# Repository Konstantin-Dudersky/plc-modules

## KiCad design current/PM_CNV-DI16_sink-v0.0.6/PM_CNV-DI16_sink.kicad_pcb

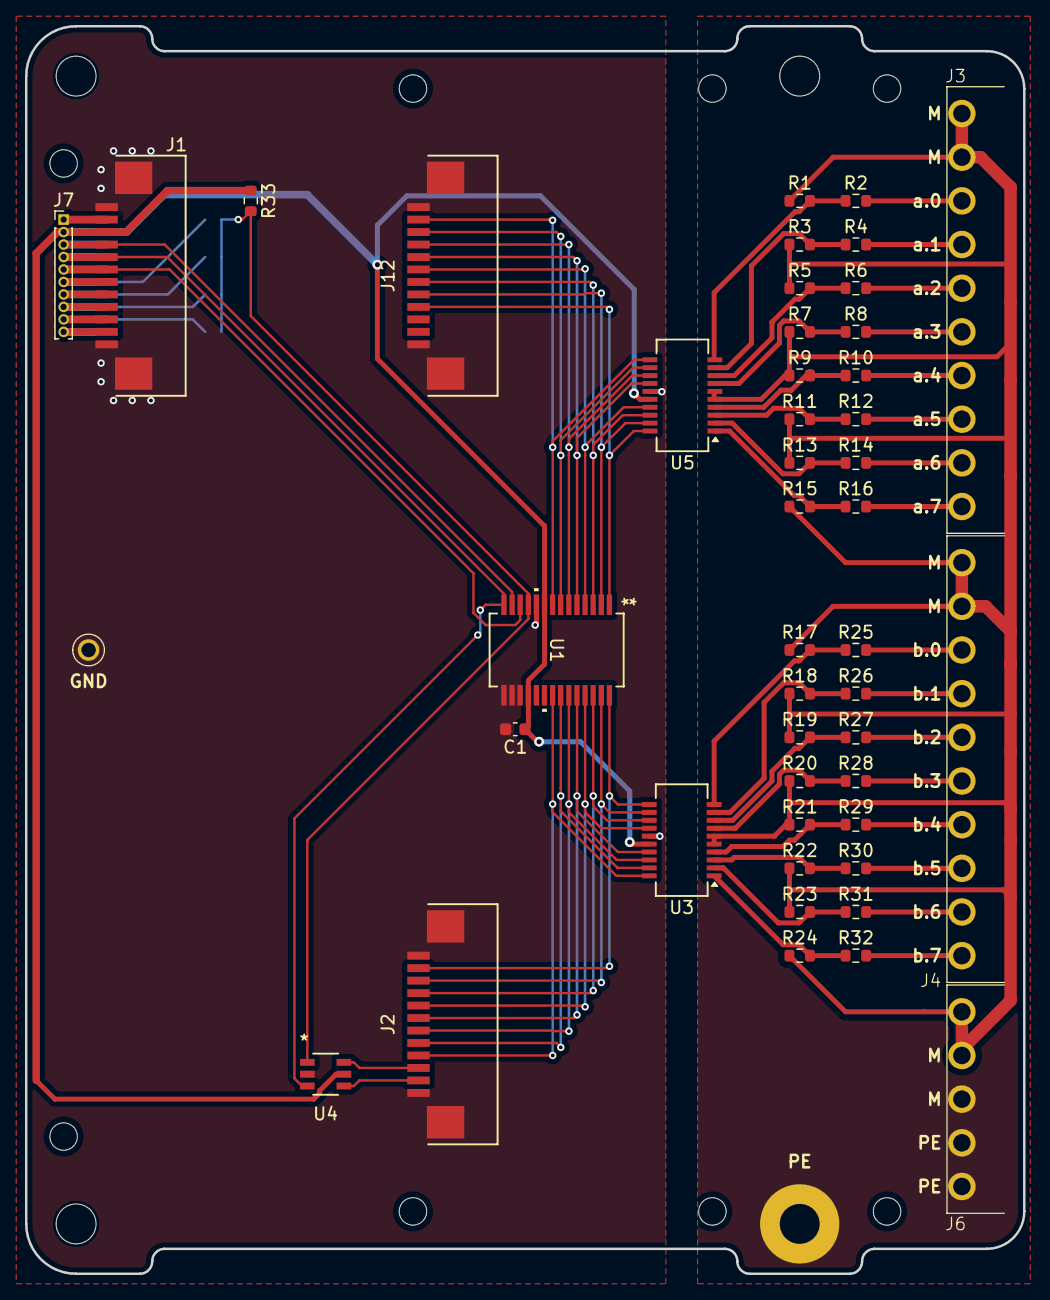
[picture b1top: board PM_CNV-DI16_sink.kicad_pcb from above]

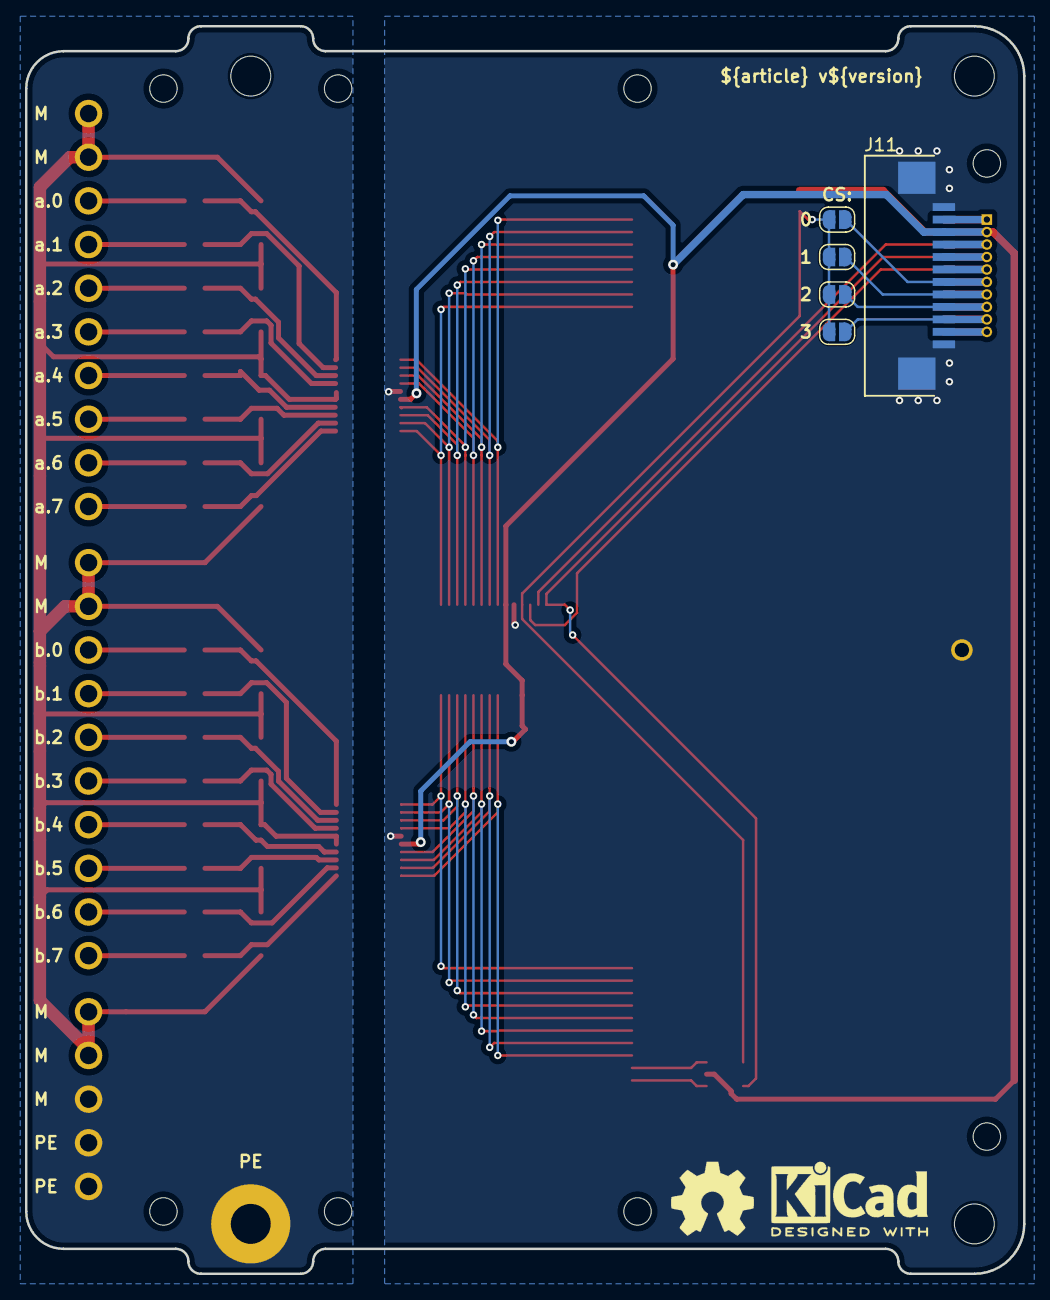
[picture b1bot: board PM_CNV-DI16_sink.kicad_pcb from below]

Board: 2 copper layers, 80.0 x 100.0 mm, 59 parts (7 on the bottom side), 64 nets.

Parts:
C1: 100nF; C_0603_1608Metric
H1, H2, H3: MountingHole; MountingHole_3.2mm_M3
J1, J2, J11, J12: AFA07-S12FCC-00; CONN10_AFA07-S12_JUS
J3, J4: 15EDGRC-3.5-10P
J6: 15EDGRC-3.5-05P
J7: PinHeader_01x10_P1.00_THT_straight; PinHeader_1x10_P1.00mm_Vertical
JP1, JP2, JP3, JP4: SolderJumper_2_Open; SolderJumper-2_P1.3mm_Open_RoundedPad1.0x1.5mm
PE1: PE
R1, R3, R5, R7, R9, R11, R13, R15, R17, R18, R19, R20, R21, R22, R23, R24: 750R; R_0603_1608Metric
R2, R4, R6, R8, R10, R12, R14, R16, R25, R26, R27, R28, R29, R30, R31, R32: 2k7; R_0603_1608Metric
R33: 10k; R_0603_1608Metric
SP1: PM_LED-xx-v0.0.1
U1: MCP23S17_SS; SSOP28_MC_MCH
U2: PM-ESP32C3_v0.0.5
U3, U5: CA-IS3980P; SSOP-20_3.9x8.7mm_P0.635mm
U4: SN74LVC2G14DBVR; DBV6-M
U6: 5117
kicad_logo: KiCad-Logo2_5mm_SilkScreen
oshw_logo: OSHW-Symbol_6.7x6mm_SilkScreen

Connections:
+3.3V_MCU: C1.1, J1.10, J7.2, J11.3, R33.1, U1.9 (VDD), U1.18 (~RESET), U3.16 (VDD), U4.5 (VCC), U5.16 (VDD)
+5V: J1.11, J7.1, J11.2
/CS: JP1.2 (B), JP2.2 (B), JP3.2 (B), JP4.2 (B), R33.2, U1.11 (~CS), U4.1 (1A)
/CS0: J1.6, J7.6, J11.7, JP1.1 (A)
/CS1: J1.5, J7.7, J11.8, JP2.1 (A)
/CS2: J1.4, J7.8, J11.9, JP3.1 (A)
/CS3: J1.3, J7.9, J11.10, JP4.1 (A)
/CS_LED: J2.3, U4.6 (1Y)
/GND_CNV: J3.9, J3.10, J4.9, J4.10, J6.4, J6.5, R1.1, R3.1, R5.1, R7.1, R9.1, R11.1, R13.1, R15.1, R17.1, R18.1, R19.1, R20.1, R21.1, R22.1, R23.1, R24.1, U3.5 (COM), U3.6 (COM), U5.5 (COM), U5.6 (COM)
/INT: J1.2, J7.10, J11.11
/MISO: J1.8, J7.4, J11.5, U1.14 (SO), U4.3 (2A)
/MISO_LED: J2.2, U4.4 (2Y)
/MOSI: J1.9, J7.3, J11.4, U1.13 (SI)
/PE: J6.1, J6.2, J6.3, PE1.1
/SCK: J1.7, J7.5, J11.6, U1.12 (SCK)
/a.0: J12.11, U1.8 (GPB7), U5.11 (B8)
/a.0_div: R1.2, R2.1, U5.10 (A8)
/a.0_in: J3.8, R2.2
/a.1: J12.10, U1.7 (GPB6), U5.12 (B7)
/a.1_div: R3.2, R4.1, U5.9 (A7)
/a.1_in: J3.7, R4.2
/a.2: J12.9, U1.6 (GPB5), U5.13 (B6)
/a.2_div: R5.2, R6.1, U5.8 (A6)
/a.2_in: J3.6, R6.2
/a.3: J12.8, U1.5 (GPB4), U5.14 (B5)
/a.3_div: R7.2, R8.1, U5.7 (A5)
/a.3_in: J3.5, R8.2
/a.4: J12.7, U1.4 (GPB3), U5.17 (B4)
/a.4_div: R9.2, R10.1, U5.4 (A4)
/a.4_in: J3.4, R10.2
/a.5: J12.6, U1.3 (GPB2), U5.18 (B3)
/a.5_div: R11.2, R12.1, U5.3 (A3)
/a.5_in: J3.3, R12.2
/a.6: J12.5, U1.2 (GPB1), U5.19 (B2)
/a.6_div: R13.2, R14.1, U5.2 (A2)
/a.6_in: J3.2, R14.2
/a.7: J12.4, U1.1 (GPB0), U5.20 (B1)
/a.7_div: R15.2, R16.1, U5.1 (A1)
/a.7_in: J3.1, R16.2
/b.0: J2.11, U1.28 (GPA7), U3.11 (B8)
/b.0_div: R17.2, R25.1, U3.10 (A8)
/b.0_in: J4.8, R25.2
/b.1: J2.10, U1.27 (GPA6), U3.12 (B7)
/b.1_div: R18.2, R26.1, U3.9 (A7)
/b.1_in: J4.7, R26.2
/b.2: J2.9, U1.26 (GPA5), U3.13 (B6)
/b.2_div: R19.2, R27.1, U3.8 (A6)
/b.2_in: J4.6, R27.2
/b.3: J2.8, U1.25 (GPA4), U3.14 (B5)
/b.3_div: R20.2, R28.1, U3.7 (A5)
/b.3_in: J4.5, R28.2
/b.4: J2.7, U1.24 (GPA3), U3.17 (B4)
/b.4_div: R21.2, R29.1, U3.4 (A4)
/b.4_in: J4.4, R29.2
/b.5: J2.6, U1.23 (GPA2), U3.18 (B3)
/b.5_div: R22.2, R30.1, U3.3 (A3)
/b.5_in: J4.3, R30.2
/b.6: J2.5, U1.22 (GPA1), U3.19 (B2)
/b.6_div: R23.2, R31.1, U3.2 (A2)
/b.6_in: J4.2, R31.2
/b.7: J2.4, U1.21 (GPA0), U3.20 (B1)
/b.7_div: R24.2, R32.1, U3.1 (A1)
/b.7_in: J4.1, R32.2
GND_MCU: C1.2, J1.1, J1.12 (Pin_11), J1.13 (Pin_11), J2.1, J2.12 (Pin_11), J2.13 (Pin_11), J11.1, J11.12 (Pin_11), J11.13 (Pin_11), J12.1, J12.12 (Pin_11), J12.13 (Pin_11), U1.10 (VSS), U1.15 (A0), U1.16 (A1), U1.17 (A2), U3.15 (GND), U4.2 (GND), U5.15 (GND), U6.1

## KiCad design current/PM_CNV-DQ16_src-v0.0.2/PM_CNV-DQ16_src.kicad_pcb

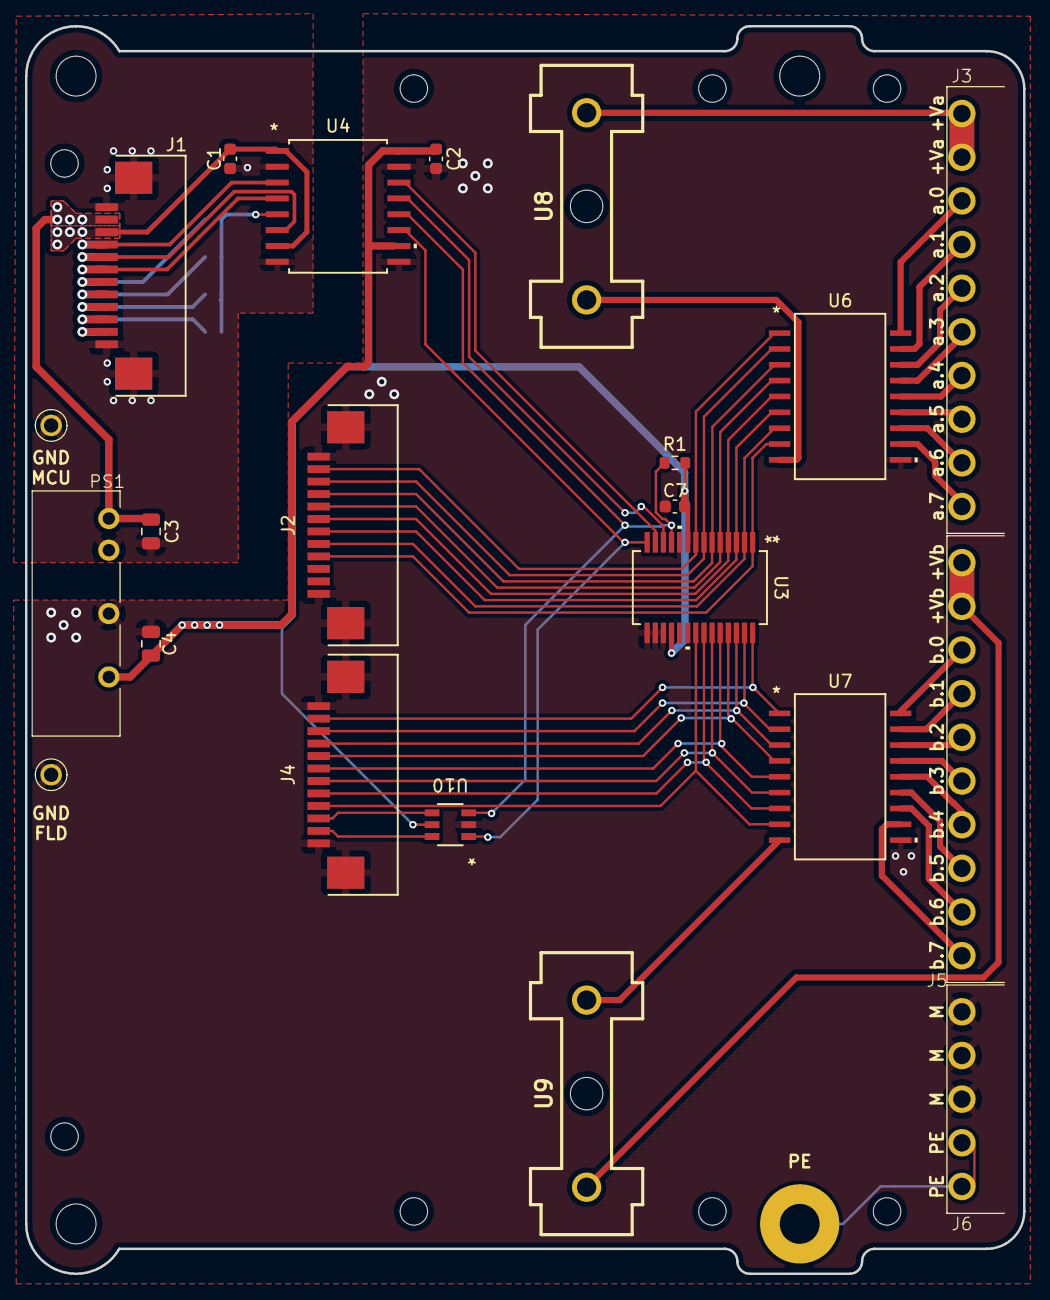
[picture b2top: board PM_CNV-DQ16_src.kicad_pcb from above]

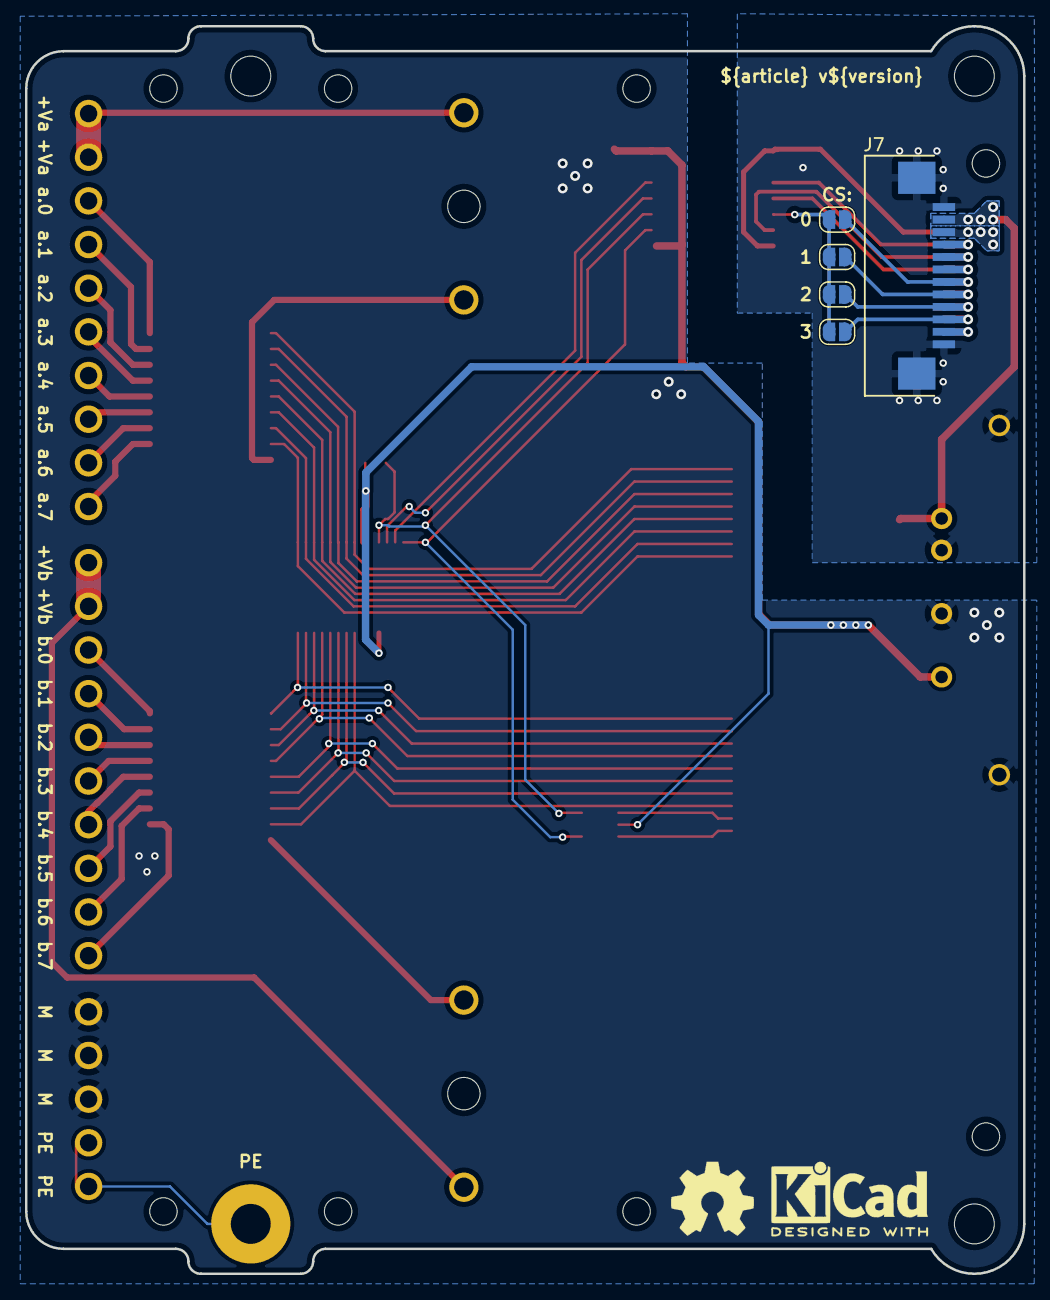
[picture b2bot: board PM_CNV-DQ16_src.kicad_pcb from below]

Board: 2 copper layers, 80.0 x 100.0 mm, 35 parts (7 on the bottom side), 57 nets.

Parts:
C1, C2, C7: 100nF; C_0603_1608Metric
C3: 4.7uF; C_0805_2012Metric
C4: 10uF; C_0805_2012Metric
H1, H2, H3: MountingHole_M3
J1, J2, J4, J7: AFA07-S12FCC-00; CONN10_AFA07-S12_JUS
J3, J5: 15EDGRC-3.5-10P
J6: 15EDGRC-3.5-05P
JP1, JP2, JP3, JP4: SolderJumper_2_Open; SolderJumper-2_P1.3mm_Open_RoundedPad1.0x1.5mm
PE1: PE
PS1: 5V/5V; B2405LS-1WR3
R1: 10k; R_0603_1608Metric
SP1: PM_LED-xx-v0.0.1
U1: PM-ESP32C3_v0.0.5
U2, U5: 5117
U3: MCP23017_SS; SSOP28_MC_MCH
U4: CA-IS3741HW; SOIC16-WBW_CLG-M
U6, U7: TBD62783AFG; SOP18-P-375-1p27_TOS-M
U8, U9: 64900001039; 649-Series-Holder
U10: SN74LVC2G14DBVR; DBV6-M
kicad_logo: KiCad-Logo2_5mm_SilkScreen
oshw_logo: OSHW-Symbol_6.7x6mm_SilkScreen

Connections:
+3.3V_MCU: C1.1, J1.10, J7.3, U4.1 (VDD), U4.7 (ENA)
+5V_CNV: C2.1, C4.1, C7.1, PS1.6 (+V), R1.1, U3.9 (VDD), U3.18 (~RESET), U4.10 (ENB), U4.16 (VISO), U10.5 (VCC)
+5V_MCU: C3.1, J1.11, J7.2, PS1.1 (Vin)
+V_a: J3.9, J3.10, U8.2
+V_b: J5.9, J5.10, U9.2
/CS: JP1.2 (B), JP2.2 (B), JP3.2 (B), JP4.2 (B), U4.5 (VI3)
/CS0: J1.6, J7.7, JP1.1 (A)
/CS1: J1.5, J7.8, JP2.1 (A)
/CS2: J1.4, J7.9, JP3.1 (A)
/CS3: J1.3, J7.10, JP4.1 (A)
/CS_CNV: R1.2, U3.11 (~CS), U4.12 (VO3), U10.3 (2A)
/CS_LED: J4.3, U10.4 (2Y)
/INT: J1.2, J7.11
/MISO: J1.8, J7.5, U4.6 (VO4)
/MISO_CNV: U3.14 (SO), U4.11 (VI4), U10.1 (1A)
/MISO_LED: J4.2, U10.6 (1Y)
/MOSI: J1.9, J7.4, U4.3 (VI1)
/MOSI_CNV: U3.13 (SI), U4.14 (VO1)
/PE: J6.1, J6.2, PE1.1
/SCK: J1.7, J7.6, U4.4 (VI2)
/SCK_CNV: U3.12 (SCK), U4.13 (VO2)
/a.0_in: J2.11, U3.8 (GPB7), U6.1 (I1)
/a.0_out: J3.8, U6.18 (O1)
/a.1_in: J2.10, U3.7 (GPB6), U6.2 (I2)
/a.1_out: J3.7, U6.17 (O2)
/a.2_in: J2.9, U3.6 (GPB5), U6.3 (I3)
/a.2_out: J3.6, U6.16 (O3)
/a.3_in: J2.8, U3.5 (GPB4), U6.4 (I4)
/a.3_out: J3.5, U6.15 (O4)
/a.4_in: J2.7, U3.4 (GPB3), U6.5 (I5)
/a.4_out: J3.4, U6.14 (O5)
/a.5_in: J2.6, U3.3 (GPB2), U6.6 (I6)
/a.5_out: J3.3, U6.13 (O6)
/a.6_in: J2.5, U3.2 (GPB1), U6.7 (I7)
/a.6_out: J3.2, U6.12 (O7)
/a.7_in: J2.4, U3.1 (GPB0), U6.8 (I8)
/a.7_out: J3.1, U6.11 (O8)
/b.0_in: J4.11, U3.28 (GPA7), U7.1 (I1)
/b.0_out: J5.8, U7.18 (O1)
/b.1_in: J4.10, U3.27 (GPA6), U7.2 (I2)
/b.1_out: J5.7, U7.17 (O2)
/b.2_in: J4.9, U3.26 (GPA5), U7.3 (I3)
/b.2_out: J5.6, U7.16 (O3)
/b.3_in: J4.8, U3.25 (GPA4), U7.4 (I4)
/b.3_out: J5.5, U7.15 (O4)
/b.4_in: J4.7, U3.24 (GPA3), U7.5 (I5)
/b.4_out: J5.4, U7.14 (O5)
/b.5_in: J4.6, U3.23 (GPA2), U7.6 (I6)
/b.5_out: J5.3, U7.13 (O6)
/b.6_in: J4.5, U3.22 (GPA1), U7.7 (I7)
/b.6_out: J5.2, U7.12 (O7)
/b.7_in: J4.4, U3.21 (GPA0), U7.8 (I8)
/b.7_out: J5.1, U7.11 (O8)
GND_CNV: C2.2, C4.2, C7.2, J2.1, J2.12 (Pin_11), J2.13 (Pin_11), J4.1, J4.12 (Pin_11), J4.13 (Pin_11), J6.3, J6.4, J6.5, PS1.4 (0V), U3.10 (VSS), U3.15 (A0), U3.16 (A1), U3.17 (A2), U4.9 (GNDB), U4.15 (GNDB), U5.1, U6.10 (GND), U7.10 (GND), U10.2 (GND)
GND_MCU: C1.2, C3.2, J1.1, J1.12 (Pin_11), J1.13 (Pin_11), J7.1, J7.12 (Pin_11), J7.13 (Pin_11), PS1.2 (GND), U2.1, U4.2 (GNDA), U4.8 (GNDA)
unnamed: U6.9 (VCC), U8.1
unnamed: U7.9 (VCC), U9.1

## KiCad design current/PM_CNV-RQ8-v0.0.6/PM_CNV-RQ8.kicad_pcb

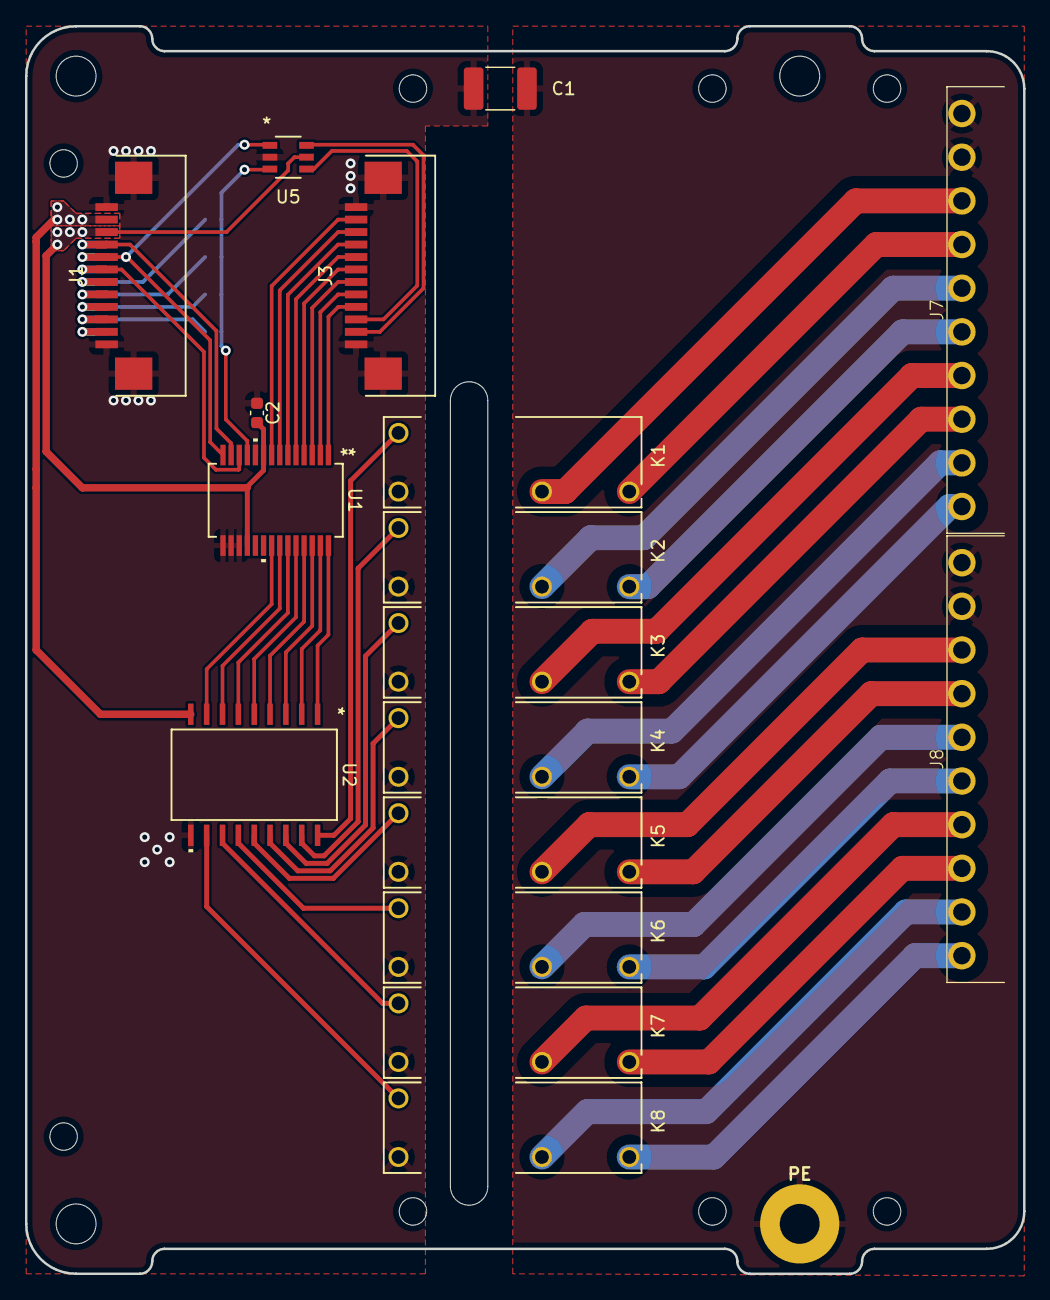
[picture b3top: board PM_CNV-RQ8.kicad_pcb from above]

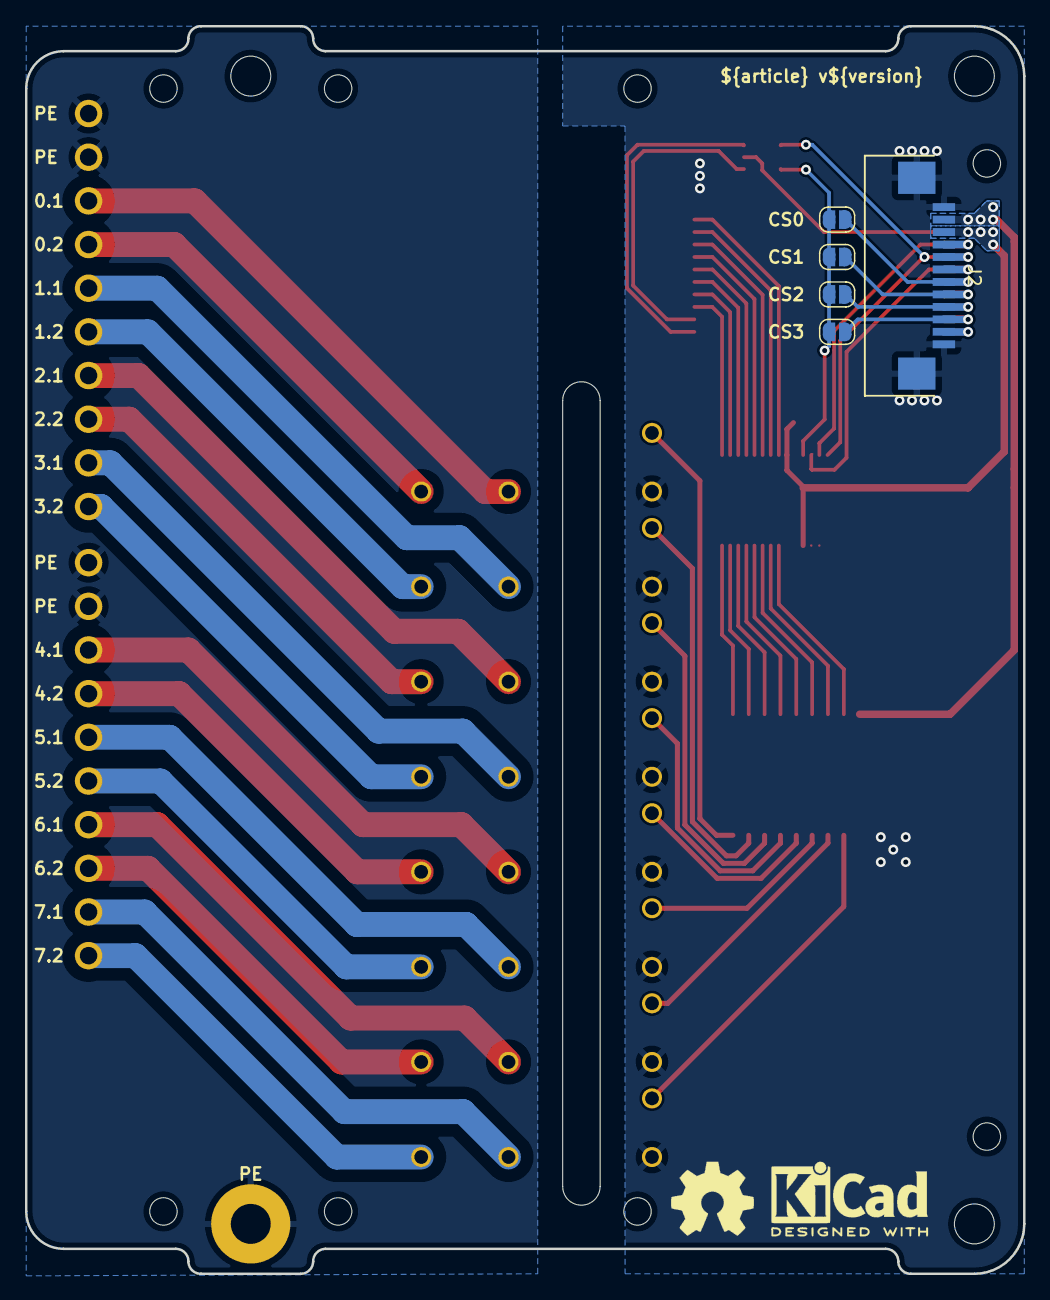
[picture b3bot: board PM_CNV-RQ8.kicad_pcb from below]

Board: 2 copper layers, 80.0 x 100.0 mm, 30 parts (7 on the bottom side), 55 nets.

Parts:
C1: 4.7nF 2kV; C_1812_4532Metric_Pad1.57x3.40mm_HandSolder
C2: 100nF; C_0603_1608Metric
H1, H2, H3: MountingHole_M3
J1, J2, J3: AFA07-S12FCC-00; CONN10_AFA07-S12_JUS
J7, J8: 15EDGRC-3.5-10P
JP1, JP2, JP3, JP4: SolderJumper_2_Open; SolderJumper-2_P1.3mm_Open_RoundedPad1.0x1.5mm
K1, K2, K3, K4, K5, K6, K7, K8: G5NB-1A-E-DC5; G5NB-1A-E_DC12_RELAY_G5NB-1A_DC5_OMR
PE1: PE
U1: MCP23S17_SS; SSOP28_MC_MCH
U2: TBD62783AFG; SOP18-P-375-1p27_TOS-M
U3: PM-LED8_v0.0.2; PM_LED-xx-v0.0.1
U4: PM-ESP32C3_v0.0.5
U5: SN74LVC2G14DBVR; DBV6-M
kicad_logo: KiCad-Logo2_5mm_SilkScreen
oshw_logo: OSHW-Symbol_6.7x6mm_SilkScreen

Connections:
+3.3V_MCU: C2.1, J1.10, J2.3, U1.9 (VDD), U1.18 (~RESET), U5.5 (VCC)
+5V_MCU: J1.11, J2.2, U2.9 (VCC)
/CS: JP1.2 (B), JP2.2 (B), JP3.2 (B), JP4.2 (B), U1.11 (~CS), U5.3 (2A)
/CS0: J1.6, J2.7, JP1.1 (A)
/CS1: J1.5, J2.8, JP2.1 (A)
/CS2: J1.4, J2.9, JP3.1 (A)
/CS3: J1.3, J2.10, JP4.1 (A)
/CS_LED: J3.3, U5.4 (2Y)
/INT: J1.2, J2.11
/K1: K1.4, U2.18 (O1)
/K1_exp: U1.28 (GPA7), U2.1 (I1)
/K1_led: J3.11, U1.8 (GPB7)
/K2: K2.4, U2.17 (O2)
/K2_exp: U1.27 (GPA6), U2.2 (I2)
/K2_led: J3.10, U1.7 (GPB6)
/K3: K3.4, U2.16 (O3)
/K3_exp: U1.26 (GPA5), U2.3 (I3)
/K3_led: J3.9, U1.6 (GPB5)
/K4: K4.4, U2.15 (O4)
/K4_exp: U1.25 (GPA4), U2.4 (I4)
/K4_led: J3.8, U1.5 (GPB4)
/K5: K5.4, U2.14 (O5)
/K5_exp: U1.24 (GPA3), U2.5 (I5)
/K5_led: J3.7, U1.4 (GPB3)
/K6: K6.4, U2.13 (O6)
/K6_exp: U1.23 (GPA2), U2.6 (I6)
/K6_led: J3.6, U1.3 (GPB2)
/K7: K7.4, U2.12 (O7)
/K7_exp: U1.22 (GPA1), U2.7 (I7)
/K7_led: J3.5, U1.2 (GPB1)
/K8: K8.4, U2.11 (O8)
/K8_exp: U1.21 (GPA0), U2.8 (I8)
/K8_led: J3.4, U1.1 (GPB0)
/MISO: J1.8, J2.5, U1.14 (SO), U5.1 (1A)
/MISO_LED: J3.2, U5.6 (1Y)
/MOSI: J1.9, J2.4, U1.13 (SI)
/SCK: J1.7, J2.6, U1.12 (SCK)
GND_MCU: C1.2, C2.2, J1.1, J1.12 (Pin_11), J1.13 (Pin_11), J2.1, J2.12 (Pin_11), J2.13 (Pin_11), J3.1, J3.12 (Pin_11), J3.13 (Pin_11), K1.1, K2.1, K3.1, K4.1, K5.1, K6.1, K7.1, K8.1, U1.10 (VSS), U1.15 (A0), U1.16 (A1), U1.17 (A2), U2.10 (GND), U5.2 (GND)
unnamed: J7.1, K4.3
unnamed: J7.2, K4.2
unnamed: J7.3, K3.3
unnamed: J7.4, K3.2
unnamed: J7.5, K2.3
unnamed: J7.6, K2.2
unnamed: J7.7, K1.3
unnamed: J7.8, K1.2
unnamed: J8.1, K8.3
unnamed: J8.2, K8.2
unnamed: J8.3, K7.3
unnamed: J8.4, K7.2
unnamed: J8.5, K6.3
unnamed: J8.6, K6.2
unnamed: J8.7, K5.3
unnamed: J8.8, K5.2
PE: C1.1, J7.9, J7.10, J8.9, J8.10, PE1.1

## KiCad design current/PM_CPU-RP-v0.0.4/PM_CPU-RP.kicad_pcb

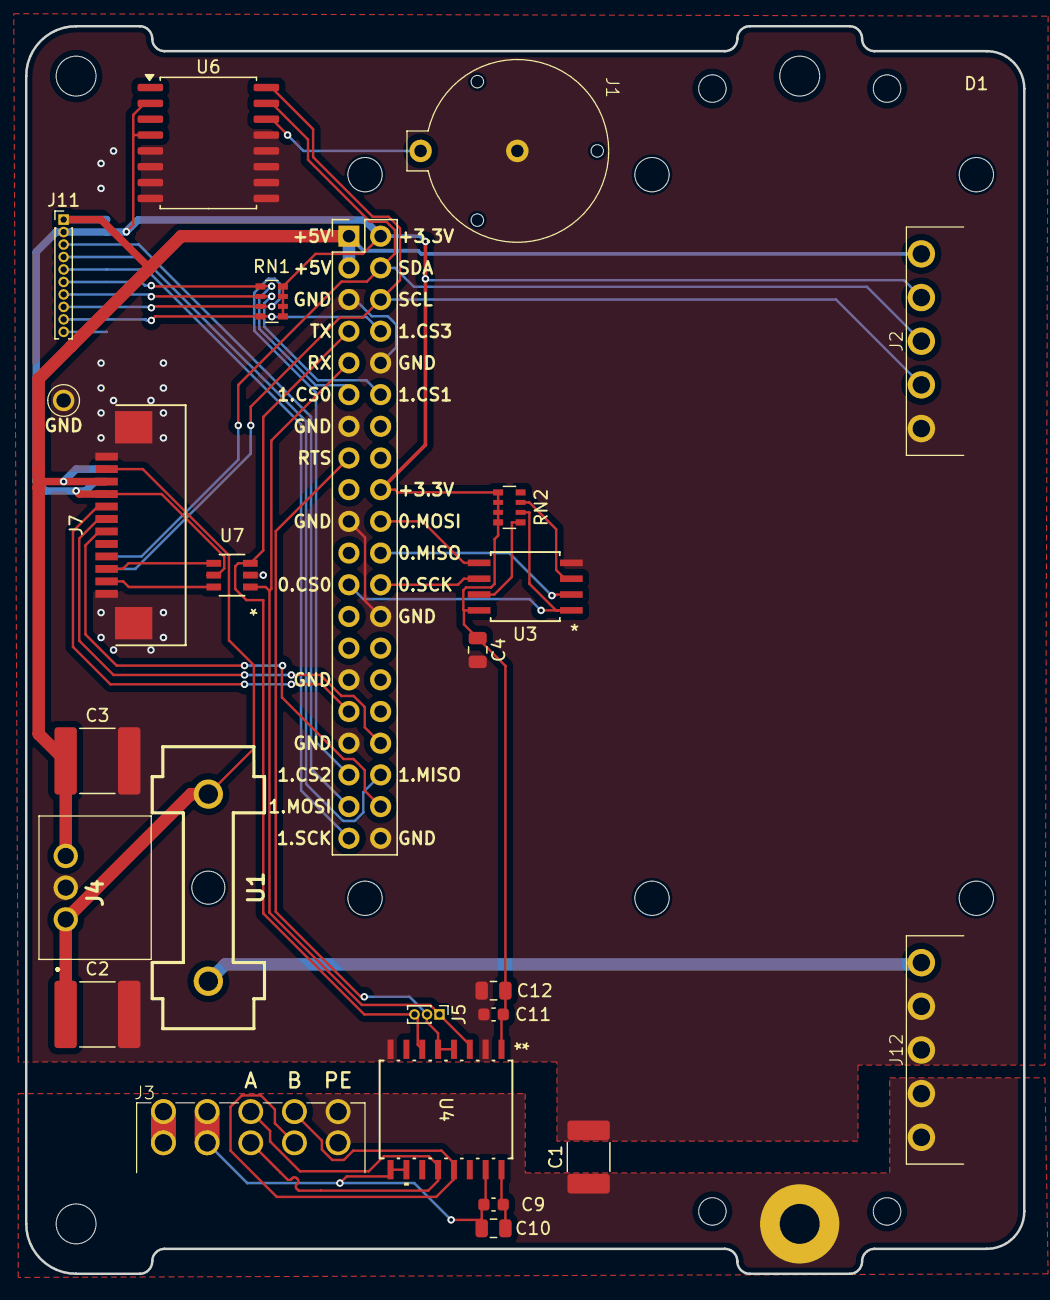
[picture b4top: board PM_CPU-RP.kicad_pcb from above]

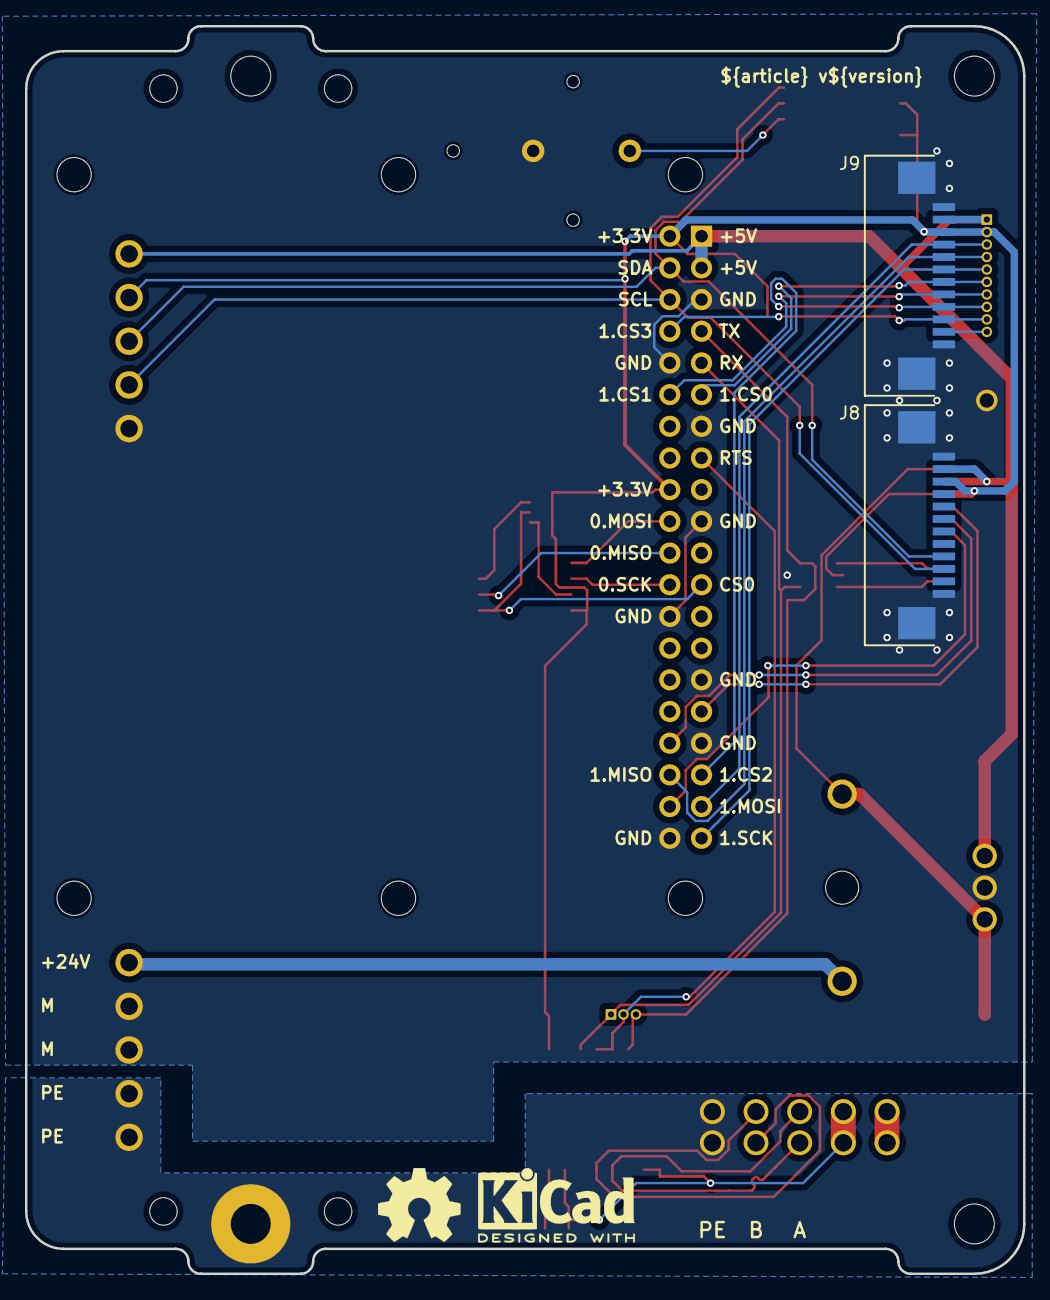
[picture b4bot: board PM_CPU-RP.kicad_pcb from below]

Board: 2 copper layers, 80.0 x 100.0 mm, 34 parts (4 on the bottom side), 36 nets.

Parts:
C1: 4.7nF 2kV; C_1812_4532Metric_Pad1.57x3.40mm_HandSolder
C2, C3: 22uF; C_2220_5750Metric
C4, C10, C12: 10uF; C_0805_2012Metric
C9, C11: 100nF; C_0603_1608Metric
D1: RaspberryPi
H1, H2, H3: MountingHole_M3
J1: BS-12-A1AJ002-F
J2, J12: 15EDGRC-3.5-05P
J3: 15EDGRHC-THR-3.5-10P
J4: K7805-2000R3
J5: PinHeader_01x03_P1.00_THT_straight; PinHeader_1x03_P1.00mm_Vertical
J7, J8, J9: AFA07-S10FCC-00; CONN10_AFA07-S12_JUS
J11: PinHeader_01x10_P1.00_THT_straight; PinHeader_1x10_P1.00mm_Vertical
PE1: PE
RN1, RN2: 10k; R_Array_Convex_4x0603
SP1: PM_LED-xx-v0.0.1
U1: 64900001039; Fuseholder
U2: 5117
U3: W25Q32JVSSIQ; SOIC-8_5P28X5P28_WIN-M
U4: CA-IS3098W; SOIC16-WBW_CLG
U6: DS3231; SOIC-16W_7.5x10.3mm_P1.27mm
U7: SN74LVC2G14DBVR; DBV6-M
kicad_logo: KiCad-Logo2_5mm_SilkScreen
oshw_logo: OSHW-Symbol_6.7x6mm_SilkScreen

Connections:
+3.3V_BUS: C9.1, C10.1, U4.16 (VISO)
+3.3V_CPU: C4.1, C11.1, C12.1, D1.1 (3V3), D1.17 (3V3), J2.4, J7.9, J8.3, J9.3, J11.2, RN1.5 (R4.2), RN1.6 (R3.2), RN1.7 (R2.2), RN1.8 (R1.2), RN2.5 (R4.2), RN2.6 (R3.2), RN2.7 (R2.2), RN2.8 (R1.2), U3.8 (VCC), U4.1 (VDD), U6.2 (VCC), U6.4 (~RST), U7.5 (VCC)
+5V: C3.1, D1.2 (5V), D1.4 (5V), J2.5, J4.3 (+VO), J7.10, J8.2, J9.2, J11.1
+24V: J12.5, U1.1
+24V_ISO: J3.1, J3.6 (Pin_2)
+24V_fuse: C2.1, J4.1 (VIN), J7.11, U1.2
/A: J3.3, J3.8 (Pin_6), U4.12 (A)
/B: J3.4, J3.9 (Pin_8), U4.13 (B)
/LED_0: D1.32 (GPIO12/PWM0), J7.8
/LED_1: D1.33 (GPIO13/PWM1), J7.7
/LED_2: D1.37 (GPIO26), J7.6
/SCL: D1.5 (GPIO3/I2C_SCL), J2.2, J8.10, U6.16 (SCL)
/SDA: D1.3 (GPIO2/I2C_SDA), J2.3, J8.9, U6.15 (SDA)
/SPI0_CS0: D1.24 (GPIO8/SPI_CE0), RN2.2 (R2.1), U3.1 (/CS)
/SPI0_MISO: D1.21 (GPIO9/SPI_MISO), U3.2 (DO(IO1))
/SPI0_MOSI: D1.19 (GPIO10/SPI_MOSI), U3.5 (DI(IO0))
/SPI0_SCK: D1.23 (GPIO11/SPI_SCLK), U3.6 (CLK)
/SPI1_CS0: D1.12 (GPIO18/PCM_CLK), J9.7, J11.6, RN1.1 (R1.1)
/SPI1_CS1: D1.11 (GPIO17), J9.8, J11.7, RN1.2 (R2.1)
/SPI1_CS2: D1.36 (GPIO16), J9.9, J11.8, RN1.3 (R3.1)
/SPI1_CS3: D1.7 (GPIO4/GPCLK0), J9.10, J11.9, RN1.4 (R4.1)
/SPI1_MISO: D1.35 (GPIO19/PCM_FS), J9.5, J11.4
/SPI1_MOSI: D1.38 (GPIO20/PCM_DIN), J9.4, J11.3
/SPI1_SCK: D1.40 (GPIO20/PCM_DOUT), J9.6, J11.5
/UART_RTS: D1.16 (GPIO23), J5.2, U4.4 (RE), U4.5 (DE)
/UART_RX: D1.10 (GPIO15/UART_RX), J5.1, U4.3 (RO), U7.1 (1A)
/UART_TX: D1.8 (GPIO14/UART_TX), J5.3, U4.6 (DI), U7.3 (2A)
/Vbat: J1.1, U6.14 (VBAT)
GND_BUS: C9.2, C10.2, J3.2 (Pin_3), J3.7 (Pin_4), U4.9 (GNDB), U4.10 (SEL), U4.15 (GNDB)
GND_CPU: C1.2, C2.2, C3.2, C4.2, C11.2, C12.2, D1.6 (GND), D1.9 (GND), D1.14 (GND), D1.20 (GND), D1.25 (GND), D1.30 (GND), D1.34 (GND), D1.39 (GND), J1.2, J2.1, J4.2 (GND), J7.1, J7.12 (Pin_11), J7.13 (Pin_11), J8.1, J8.12 (Pin_11), J8.13 (Pin_11), J9.1, J9.12 (Pin_11), J9.13 (Pin_11), J12.3, J12.4, U2.1, U3.4 (GND), U4.2 (GNDA), U4.8 (GNDA), U6.5 (GND), U6.6 (GND), U6.7 (GND), U6.8 (GND), U6.9 (GND), U6.10 (GND), U6.11 (GND), U6.12 (GND), U6.13 (GND), U7.2 (GND)
unnamed: J7.2, U7.6 (1Y)
unnamed: J7.3, U7.4 (2Y)
unnamed: J9.11, J11.10
unnamed: RN2.1 (R1.1), U3.7 (/HOLD_(IO3))
unnamed: RN2.3 (R3.1), U3.3 (/WP(IO2))
PE: C1.1, J3.5 (Pin_9), J3.10, J12.1, J12.2, PE1.1

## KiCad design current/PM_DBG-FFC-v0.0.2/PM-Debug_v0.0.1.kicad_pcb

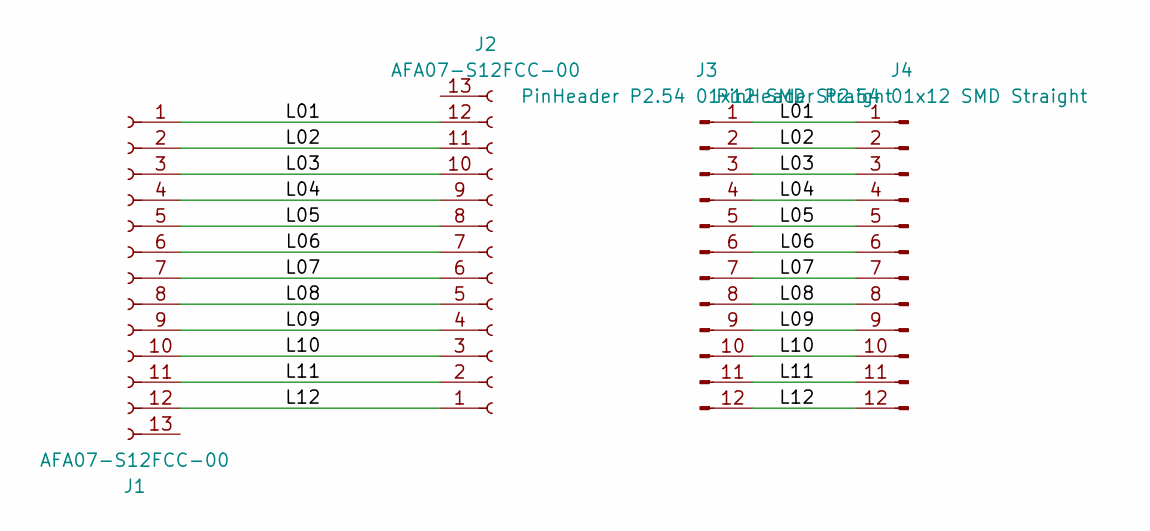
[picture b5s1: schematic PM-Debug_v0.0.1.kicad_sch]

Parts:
J1, J2: AFA07-S12FCC-00; CONN10_AFA07-S12_JUS; part_ipn AFA07-S12FCC-00
J3, J4: PinHeader P2.54 01x12 SMD Straight; PinHeader_1x12_P2.54mm_Vertical_SMD_Pin1Left; part_ipn PinHeader P2.54 01x12 SMD Straight

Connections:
/L01: J1.1, J2.12 (Pin_11), J3.1, J4.1
/L02: J1.2, J2.11, J3.2, J4.2
/L03: J1.3, J2.10, J3.3, J4.3
/L04: J1.4, J2.9, J3.4, J4.4
/L05: J1.5, J2.8, J3.5, J4.5
/L06: J1.6, J2.7, J3.6, J4.6
/L07: J1.7, J2.6, J3.7, J4.7
/L08: J1.8, J2.5, J3.8, J4.8
/L09: J1.9, J2.4, J3.9, J4.9
/L10: J1.10, J2.3, J3.10, J4.10
/L11: J1.11, J2.2, J3.11, J4.11
/L12: J1.12 (Pin_11), J2.1, J3.12, J4.12

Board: 2 copper layers, 4 parts (0 on the bottom side), 12 nets, no tracks yet.

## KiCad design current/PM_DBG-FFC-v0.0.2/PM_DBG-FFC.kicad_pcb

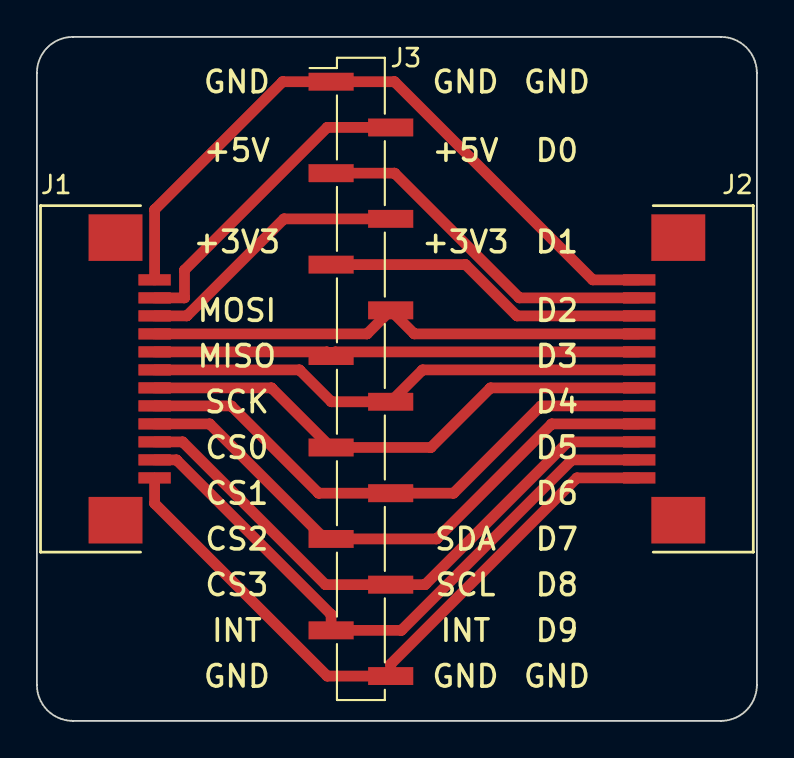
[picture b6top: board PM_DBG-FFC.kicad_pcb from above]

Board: 2 copper layers, 40.0 x 38.0 mm, 3 parts (0 on the bottom side), 14 nets.

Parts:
J1, J2: AFA07-S12FCC-00; CONN10_AFA07-S12_JUS
J3: PinHeader_01x14_P2.54_SMD_straight; PinHeader_1x14_P2.54mm_Vertical_SMD_Pin1Left

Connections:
/L01: J1.1, J2.12 (Pin_11), J3.1
/L02_in: J1.2, J3.2
/L02_out: J2.11, J3.3
/L03_in: J1.3, J3.4
/L03_out: J2.10, J3.5
/L04: J1.4, J2.9, J3.6
/L05: J1.5, J2.8, J3.7
/L06: J1.6, J2.7, J3.8
/L07: J1.7, J2.6, J3.9
/L08: J1.8, J2.5, J3.10
/L09: J1.9, J2.4, J3.11
/L10: J1.10, J2.3, J3.12
/L11: J1.11, J2.2, J3.13
/L12: J1.12 (Pin_11), J2.1, J3.14

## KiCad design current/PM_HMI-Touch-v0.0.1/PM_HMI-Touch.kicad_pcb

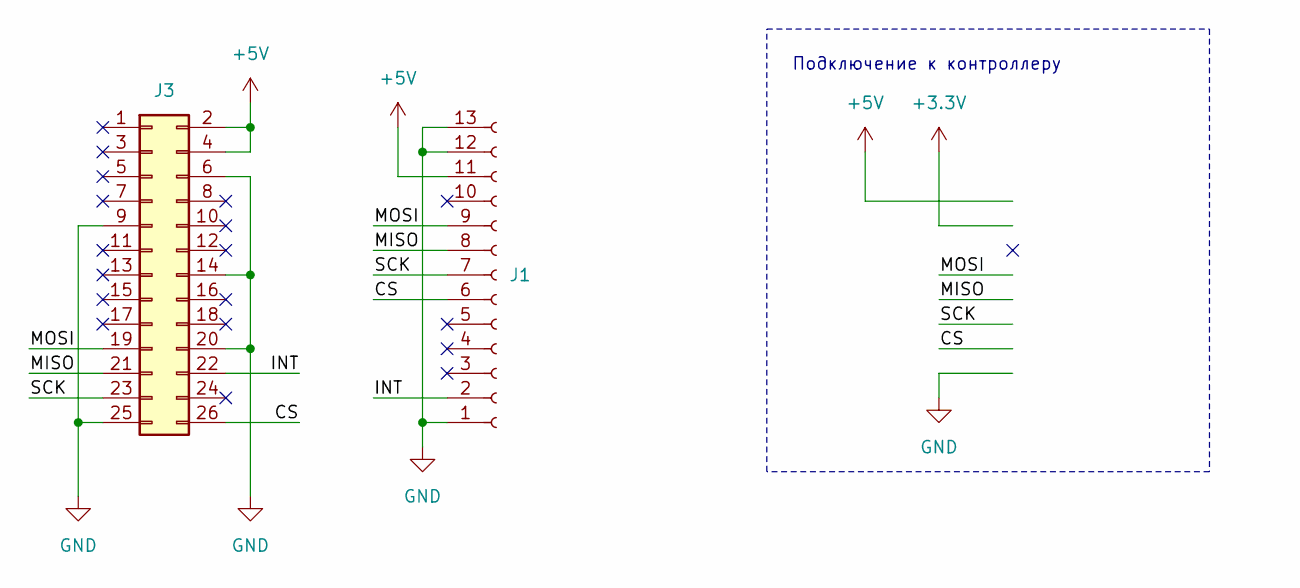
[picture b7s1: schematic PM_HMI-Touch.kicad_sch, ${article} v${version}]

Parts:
J1: AFA07-S12FCC-00; CONN10_AFA07-S12_JUS; part_ipn AFA07-S12FCC-00
J3: PinHeader_02x13_P2.54_THT_straight; PinHeader_2x13_P2.54mm_Vertical; part_ipn PinHeader_02x13_P2.54_THT_straight

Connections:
+5V: J1.11, J3.2, J3.4
/CS: J1.6, J3.26
/INT: J1.2, J3.22
/MISO: J1.8, J3.21
/MOSI: J1.9, J3.19
/SCK: J1.7, J3.23
GND: J1.1, J1.12 (Pin_11), J1.13 (Pin_11), J3.6, J3.9, J3.14, J3.20, J3.25

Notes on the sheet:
Подключение к контроллеру

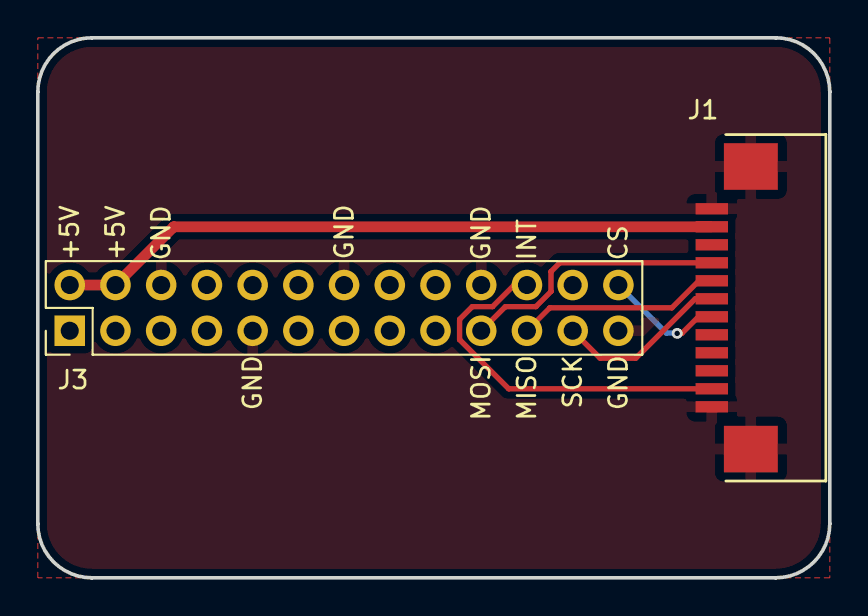
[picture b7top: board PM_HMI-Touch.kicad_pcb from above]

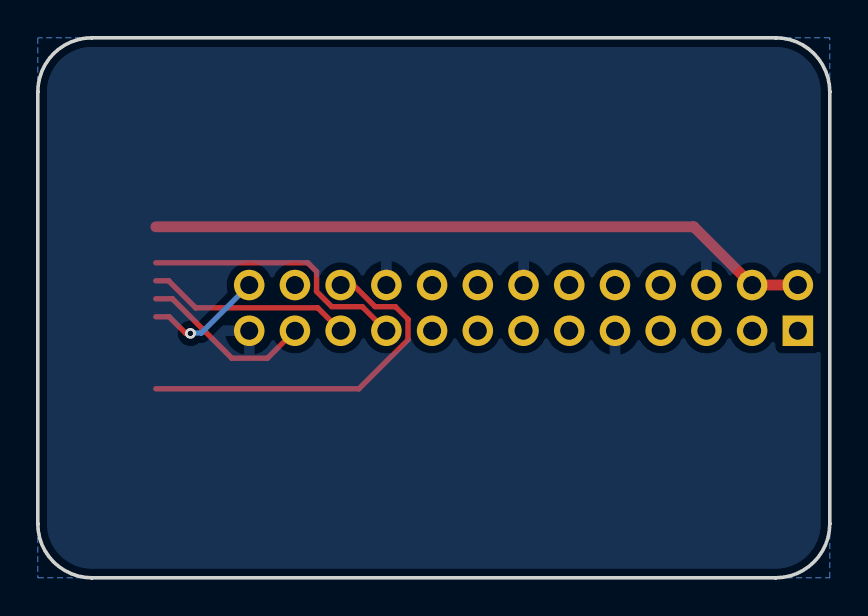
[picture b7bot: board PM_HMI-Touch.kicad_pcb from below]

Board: 2 copper layers, 44.0 x 30.0 mm, 4 parts (2 on the bottom side), 7 nets.

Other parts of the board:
kicad_logo: KiCad-Logo2_5mm_SilkScreen
oshw_logo: OSHW-Symbol_6.7x6mm_SilkScreen

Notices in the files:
parts and their libraries:
COPYRIGHT: Copyright (C) 2023 Ultra Librarian. All rights reserved.
